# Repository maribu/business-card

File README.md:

# Marian's Business Card

This repository contains an open hardware business card running open source
software.

A blogged a [detailed write up](https://mari-bu.de/blog/20240910-business-card/)
of this project. You may also want to check out the corresponding
[Hackaday.io project](https://hackaday.io/project/197871-marians-business-card).

## Getting started

### Hardware

Using KiCad, add Silkscreen details such as your name. E.g. I added my contact
details and word cloud of my skills on the back of the PCB. Using the JLCPCB
fabrication plugin of KiCAD, you can export the production files to directly
order the PCBs.

Note that when using vanilla PCB options (1.6 mm PCB thickness, HASL surface
finish) the USB connector will be a tad too thin to perfectly make contact with
a USB socket. Ideally you would use 2.0 mm PCB thickness and ENIG surface
finish, but that would be so expensive that it defeats the purpose of a
business card. Instead, you can just add a bit of solder on the USB contacts to
increase the thickness.

### Software

A simple "hello world" demo is given in
`software/RIOT-based-apps/apps/hello-world` that you can flash using e.g. a
J-Link EDU Mini programmer. Rather than using a cable, just plug the pins of
the J-Link EDU Mini programmer from the underside through the holes and rotate
the programmer until the pins and holes have contact. In addition, you need to
power the board (ideally via a USB-A extension cord).

With the programmer connected and the board powered, simply run:

    make flash

The "default" application will be `software/RIOT-based-apps/apps/games`, as
this contains a game launcher that allows running all currently added games.

Refer to the [RIOT documentation](https://doc.riot-os.org/) for more details on
the software.

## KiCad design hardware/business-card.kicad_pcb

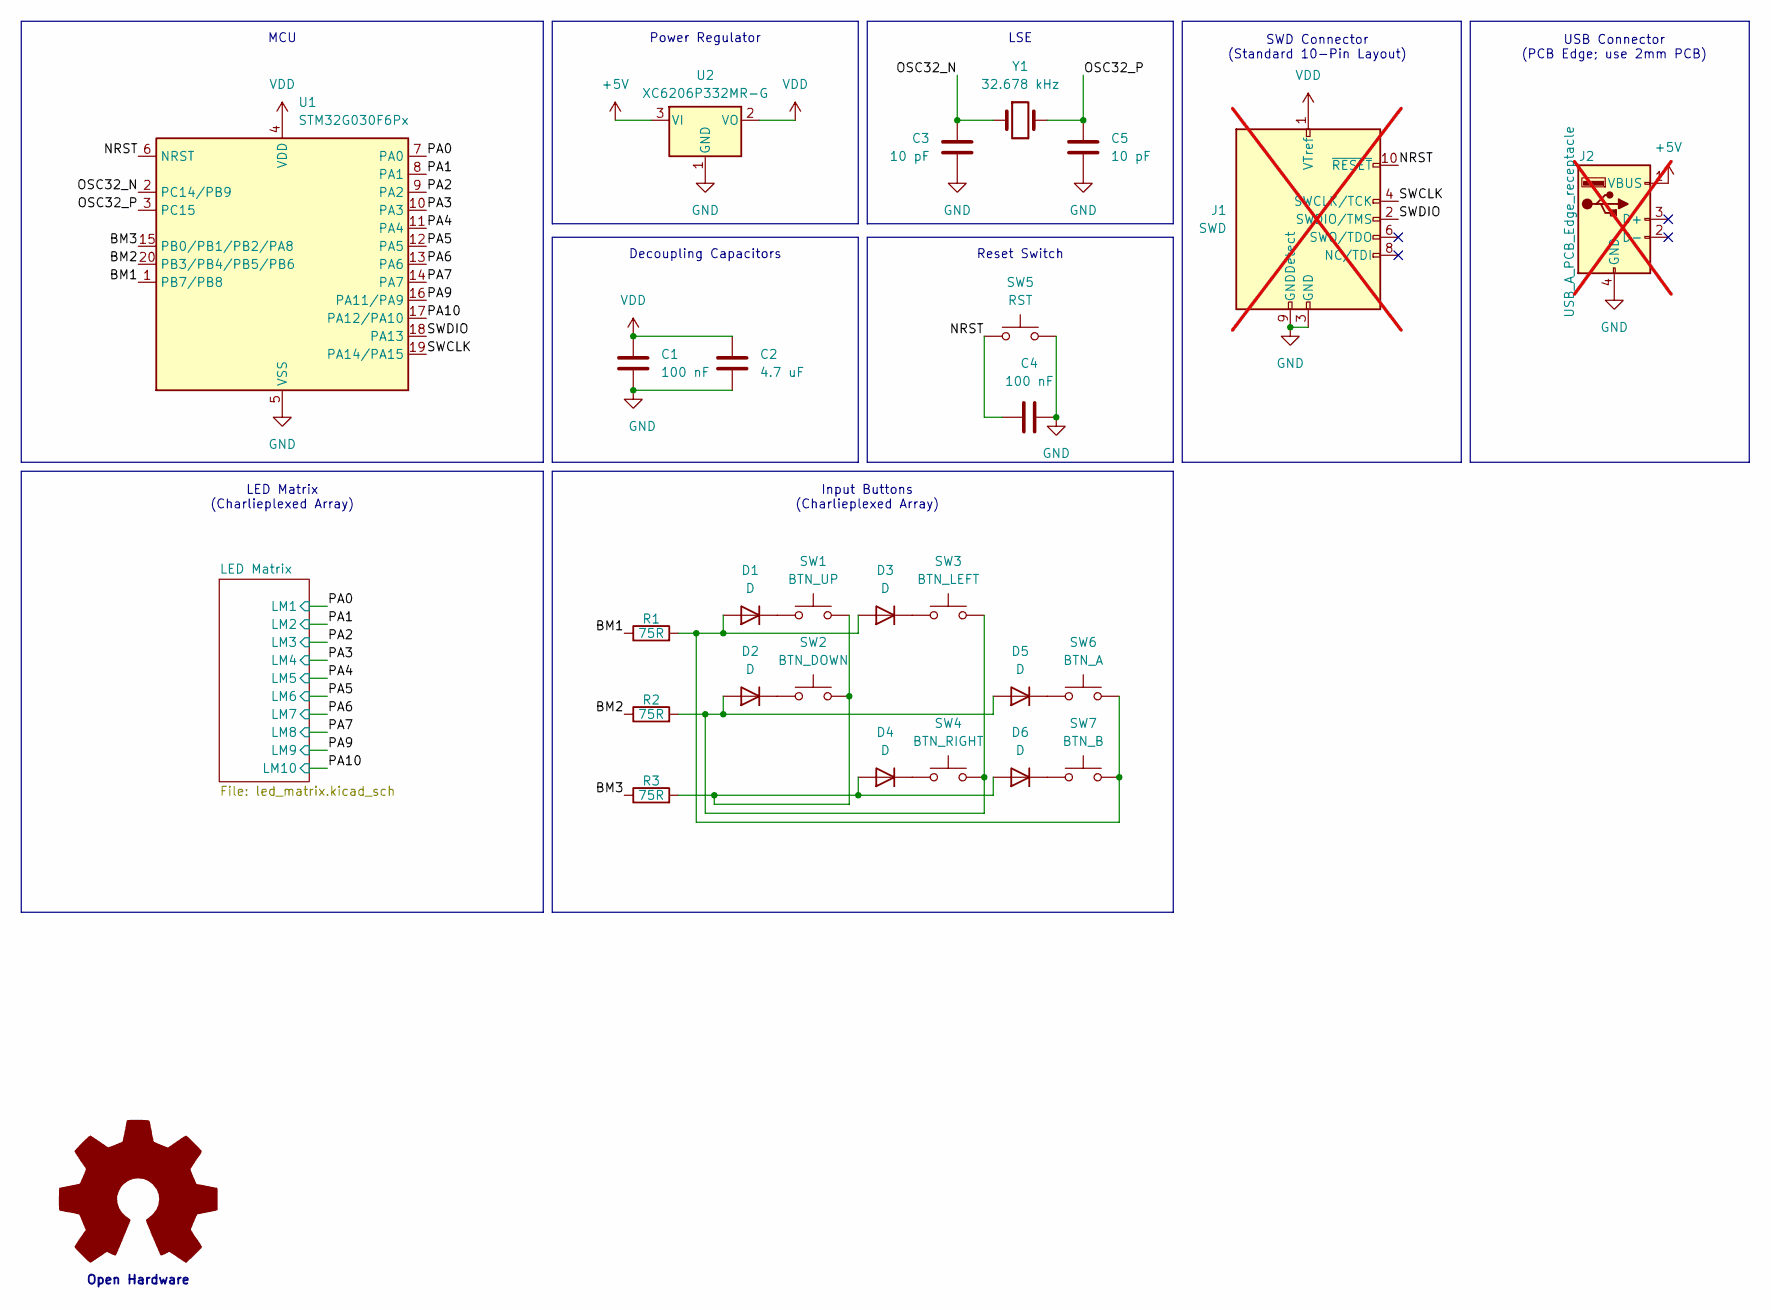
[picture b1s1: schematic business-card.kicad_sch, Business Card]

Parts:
C1, C4: 100 nF; C_0402_1005Metric; MPN C1525
C2: 4.7 uF; C_0402_1005Metric; MPN C23733
C3, C5: 10 pF; C_0402_1005Metric; MPN C32949
D1, D2, D3, D4, D5, D6: D; D_SOD-123F; MPN C64898
J1: SWD; PinHeader_2x05_P1.27mm_Vertical; not fitted
J2: USB_A_PCB_Edge_receptacle; not fitted
R1, R2, R3: 75R; R_0603_1608Metric; MPN C4275
SW1: BTN_UP; SW_Push_1P1T_XKB_TS-1187A; MPN C318884
SW2: BTN_DOWN; SW_Push_1P1T_XKB_TS-1187A; MPN C318884
SW3: BTN_LEFT; SW_Push_1P1T_XKB_TS-1187A; MPN C318884
SW4: BTN_RIGHT; SW_Push_1P1T_XKB_TS-1187A; MPN C318884
SW5: RST; SW_Push_1P1T_XKB_TS-1187A; MPN C318884
SW6: BTN_A; SW_Push_1P1T_XKB_TS-1187A; MPN C318884
SW7: BTN_B; SW_Push_1P1T_XKB_TS-1187A; MPN C318884
U1: STM32G030F6Px; TSSOP-20_4.4x6.5mm_P0.65mm; MPN C529330
U2: XC6206P332MR-G; SOT-23-3; MPN C5446
Y1: 32.678 kHz; Crystal_SMD_3215-2Pin_3.2x1.5mm; MPN C32346

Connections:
+5V: J2.1 (VBUS), U2.3 (VI)
/BM1: R1.1, U1.1 (PB7/PB8)
/BM2: R2.1, U1.20 (PB3/PB4/PB5/PB6)
/BM3: R3.1, U1.15 (PB0/PB1/PB2/PA8)
/NRST: C4.1, J1.10 (~RESET), SW5.1, U1.6 (NRST)
/OSC32_N: C3.1, U1.2 (PC14/PB9), Y1.1
/OSC32_P: C5.1, U1.3 (PC15), Y1.2
/PA0: U1.7 (PA0); also elsewhere on the board
/PA1: U1.8 (PA1); also elsewhere on the board
/PA2: U1.9 (PA2); also elsewhere on the board
/PA3: U1.10 (PA3); also elsewhere on the board
/PA4: U1.11 (PA4); also elsewhere on the board
/PA5: U1.12 (PA5); also elsewhere on the board
/PA6: U1.13 (PA6); also elsewhere on the board
/PA7: U1.14 (PA7); also elsewhere on the board
/PA9: U1.16 (PA11/PA9); also elsewhere on the board
/PA10: U1.17 (PA12/PA10); also elsewhere on the board
/SWCLK: J1.4 (SWCLK/TCK), U1.19 (PA14/PA15)
/SWDIO: J1.2 (SWDIO/TMS), U1.18 (PA13)
GND: C1.2, C2.2, C3.2, C4.2, C5.2, J1.3 (GND), J1.5 (GND), J1.9 (GNDDetect), J2.4 (GND), SW5.2, U1.5 (VSS), U2.1 (GND)
unnamed: D1.2 (A), D3.2 (A), R1.2, SW6.2, SW7.2
unnamed: D1.1 (K), SW1.1
unnamed: D2.2 (A), D5.2 (A), R2.2, SW3.2, SW4.2
unnamed: D2.1 (K), SW2.1
unnamed: D3.1 (K), SW3.1
unnamed: D4.2 (A), D6.2 (A), R3.2, SW1.2, SW2.2
unnamed: D4.1 (K), SW4.1
unnamed: D5.1 (K), SW6.1
unnamed: D6.1 (K), SW7.1
VDD: C1.1, C2.1, J1.1 (VTref), U1.4 (VDD), U2.2 (VO)

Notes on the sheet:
Input Buttons (Charlieplexed Array)
SWD Connector (Standard 10-Pin Layout)
MCU
Reset Switch
Power Regulator
LSE
Decoupling Capacitors
USB Connector (PCB Edge; use 2mm PCB)
LED Matrix (Charlieplexed Array)
Open Hardware

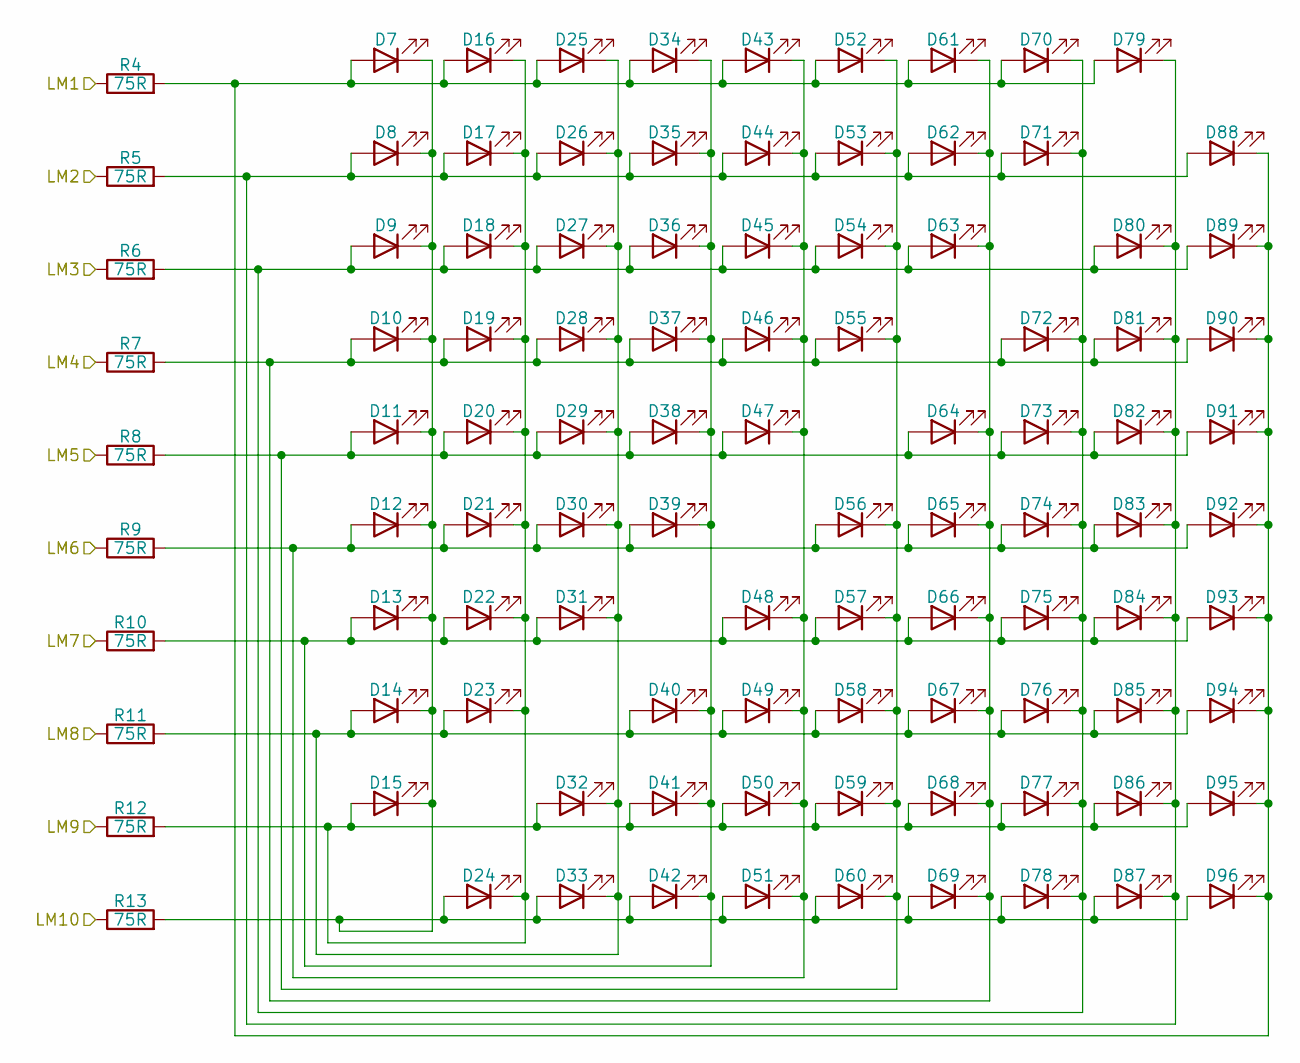
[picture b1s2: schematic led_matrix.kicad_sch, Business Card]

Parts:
D7, D8, D9, D10, D11, D12, D13, D14, D15, D16, D17, D18, D19, D20, D21, D22, D23, D24, D25, D26, D27, D28, D29, D30, D31, D32, D33, D34, D35, D36, D37, D38, D39, D40, D41, D42, D43, D44, D45, D46, D47, D48, D49, D50, D51, D52, D53, D54, D55, D56, D57, D58, D59, D60, D61, D62, D63, D64, D65, D66, D67, D68, D69, D70, D71, D72, D73, D74, D75, D76, D77, D78, D79, D80, D81, D82, D83, D84, D85, D86, D87, D88, D89, D90, D91, D92, D93, D94, D95, D96: LED; LED_0603_1608Metric; MPN C2286
R4, R5, R6, R7, R8, R9, R10, R11, R12, R13: 75R; R_0603_1608Metric; MPN C4275

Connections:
/PA0: R4.1; also elsewhere on the board
/PA1: R5.1; also elsewhere on the board
/PA2: R6.1; also elsewhere on the board
/PA3: R7.1; also elsewhere on the board
/PA4: R8.1; also elsewhere on the board
/PA5: R9.1; also elsewhere on the board
/PA6: R10.1; also elsewhere on the board
/PA7: R11.1; also elsewhere on the board
/PA9: R12.1; also elsewhere on the board
/PA10: R13.1; also elsewhere on the board
unnamed: D10.2 (A), D19.2 (A), D28.2 (A), D37.2 (A), D46.2 (A), D55.2 (A), D61.1 (K), D62.1 (K), D63.1 (K), D64.1 (K), D65.1 (K), D66.1 (K), D67.1 (K), D68.1 (K), D69.1 (K), D72.2 (A), D81.2 (A), D90.2 (A), R7.2
unnamed: D7.1 (K), D8.1 (K), D9.1 (K), D10.1 (K), D11.1 (K), D12.1 (K), D13.1 (K), D14.1 (K), D15.1 (K), D24.2 (A), D33.2 (A), D42.2 (A), D51.2 (A), D60.2 (A), D69.2 (A), D78.2 (A), D87.2 (A), D96.2 (A), R13.2
unnamed: D11.2 (A), D20.2 (A), D29.2 (A), D38.2 (A), D47.2 (A), D52.1 (K), D53.1 (K), D54.1 (K), D55.1 (K), D56.1 (K), D57.1 (K), D58.1 (K), D59.1 (K), D60.1 (K), D64.2 (A), D73.2 (A), D82.2 (A), D91.2 (A), R8.2
unnamed: D12.2 (A), D21.2 (A), D30.2 (A), D39.2 (A), D43.1 (K), D44.1 (K), D45.1 (K), D46.1 (K), D47.1 (K), D48.1 (K), D49.1 (K), D50.1 (K), D51.1 (K), D56.2 (A), D65.2 (A), D74.2 (A), D83.2 (A), D92.2 (A), R9.2
unnamed: D13.2 (A), D22.2 (A), D31.2 (A), D34.1 (K), D35.1 (K), D36.1 (K), D37.1 (K), D38.1 (K), D39.1 (K), D40.1 (K), D41.1 (K), D42.1 (K), D48.2 (A), D57.2 (A), D66.2 (A), D75.2 (A), D84.2 (A), D93.2 (A), R10.2
unnamed: D14.2 (A), D23.2 (A), D25.1 (K), D26.1 (K), D27.1 (K), D28.1 (K), D29.1 (K), D30.1 (K), D31.1 (K), D32.1 (K), D33.1 (K), D40.2 (A), D49.2 (A), D58.2 (A), D67.2 (A), D76.2 (A), D85.2 (A), D94.2 (A), R11.2
unnamed: D15.2 (A), D16.1 (K), D17.1 (K), D18.1 (K), D19.1 (K), D20.1 (K), D21.1 (K), D22.1 (K), D23.1 (K), D24.1 (K), D32.2 (A), D41.2 (A), D50.2 (A), D59.2 (A), D68.2 (A), D77.2 (A), D86.2 (A), D95.2 (A), R12.2
unnamed: D7.2 (A), D16.2 (A), D25.2 (A), D34.2 (A), D43.2 (A), D52.2 (A), D61.2 (A), D70.2 (A), D79.2 (A), D88.1 (K), D89.1 (K), D90.1 (K), D91.1 (K), D92.1 (K), D93.1 (K), D94.1 (K), D95.1 (K), D96.1 (K), R4.2
unnamed: D8.2 (A), D17.2 (A), D26.2 (A), D35.2 (A), D44.2 (A), D53.2 (A), D62.2 (A), D71.2 (A), D79.1 (K), D80.1 (K), D81.1 (K), D82.1 (K), D83.1 (K), D84.1 (K), D85.1 (K), D86.1 (K), D87.1 (K), D88.2 (A), R5.2
unnamed: D9.2 (A), D18.2 (A), D27.2 (A), D36.2 (A), D45.2 (A), D54.2 (A), D63.2 (A), D70.1 (K), D71.1 (K), D72.1 (K), D73.1 (K), D74.1 (K), D75.1 (K), D76.1 (K), D77.1 (K), D78.1 (K), D80.2 (A), D89.2 (A), R6.2

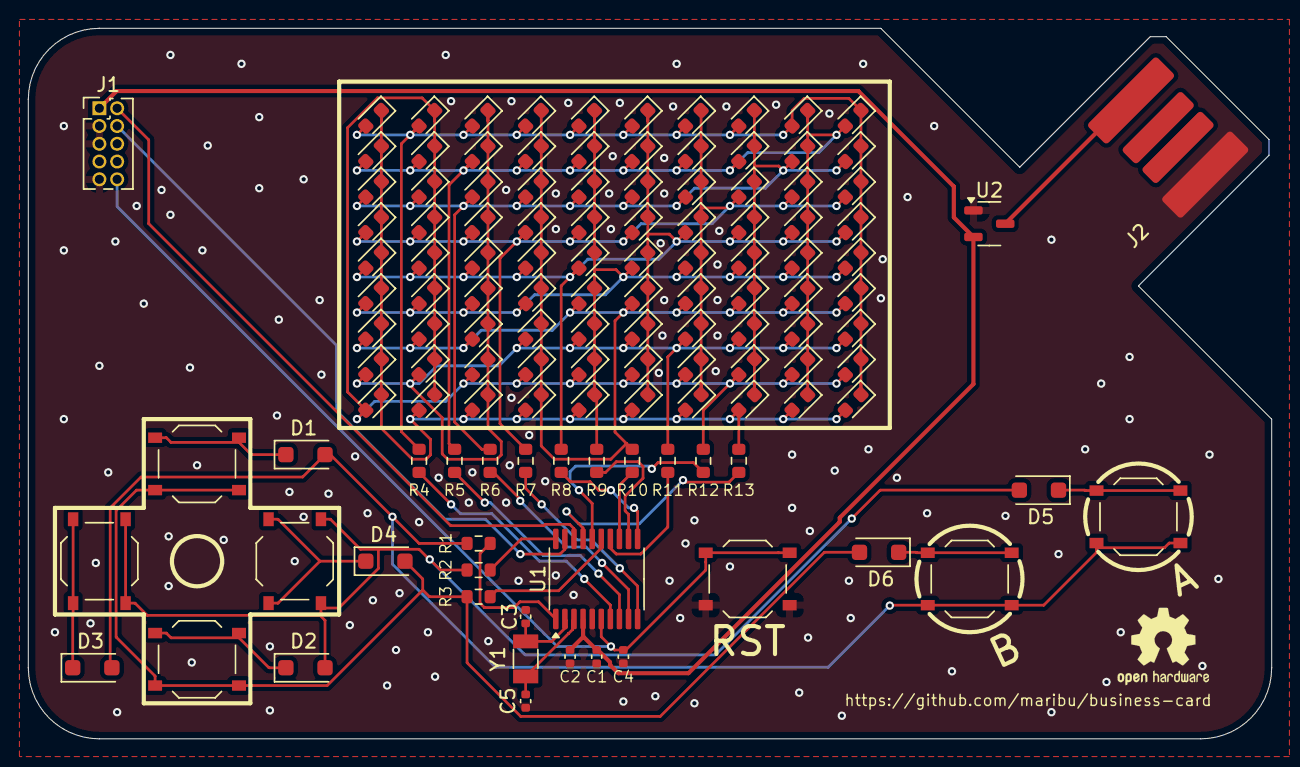
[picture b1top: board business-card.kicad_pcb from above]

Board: 2 copper layers, 88.9 x 50.8 mm, 127 parts (0 on the bottom side), 40 nets.

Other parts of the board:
G**: OSHW-Logo2_7.3x6mm_SilkScreen

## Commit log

2024-08-04 Declare licenses
2024-08-04 hardware: Add initial business card PCB
2024-08-05 software: Add RIOT based hello world example
2024-08-05 Add README.md
2024-08-07 software/RIOT*: greatly improved font rendering
    This adds a new font from the https://github.com/trip5/Matrix-Fonts
    repository and a new binary font encoding that better fits
    fonts with variable width.
    The led_matrix module has been updated to allow specifying the
    font used to render text and the API has been improved.
    A simple heuristic to detect when adding a blank column between
2024-08-07 hardware: Consistent label numbering
    Number the button matrix labels from top to bottom to match the
    numbering of the LED matrix.
    The labels on the MCU pins have been changed accordingly, so that
    this change is a no-op.
    The PCB has been updated accordingly, but other than netlist names
    nothing has changed.
2024-08-07 software/RIOT*/board: update button matrix names
    Match the numbering scheme from the schematic in the board
    file.
2024-08-09 software/RIOT*/modules/led_matrix: Improve doc
2024-08-09 software/RIOT*: Update RIOT submodule to current master
    The PR implementing gpio_ll_switch_dir for STM32 has been
    merged upstream.
2024-08-09 software/RIOT*: Add module to read out button matrix
    This adds a module to read out the button matrix and two
    demo apps. One works when at most one key is pressed at
    any point in time. The other uses a simple heuristic to
    provide 2-key-rollover input.
2024-09-09 software/RIOT*: Add "simon says" game
2024-09-09 software/RIOT*: clean up LEDmon says
    The code likely is a bit less efficient, but easier to maintain now.
2024-09-09 software/RIOT*: Increase with of space in bitmap font
2024-09-09 software/RIOT*: Moved LEDmon says to games module
2024-09-09 software/RIOT*: Add game chooser app
2024-09-09 hardware: add panelization
2024-09-09 software/RIOT*: add flappy-LED game
2024-09-09 software/RIOT*: Refactored flappy LED game
    Created an led_matrix_games module and moved the implementation of
    flappy LED there. In addition, the infrastructure to share RAM
    between multiple games has been created, so that a firmware presenting
    a menu of multiple games to pick from becomes possible.
2024-09-09 software/RIOT*: improve playability of ledmon-says
    Also move out some glyphs to the bitmap_fonts module for reuse in
    other games.
2024-09-10 README.md: Add link to blog and hackaday.io project
